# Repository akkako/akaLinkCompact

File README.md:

# akaLink Compact

* CMSIS-DAP v2.1 在线调试功能
  * SWD 接口
  * JTAG 接口
* VCOM 功能
  * 支持最高 1Mbps 收发
* 5V 输出功能
  * 支持外接隔离器

## TODO List

- [X] 移植 CMSIS-DAP
- [X] 优化 SWD 速度
- [ ] 优化 JTAG 性能
- [ ] 优化 VCOM 性能
- [ ] 更多速度选项
- [ ] Bootloader
- [X] HID 配置功能

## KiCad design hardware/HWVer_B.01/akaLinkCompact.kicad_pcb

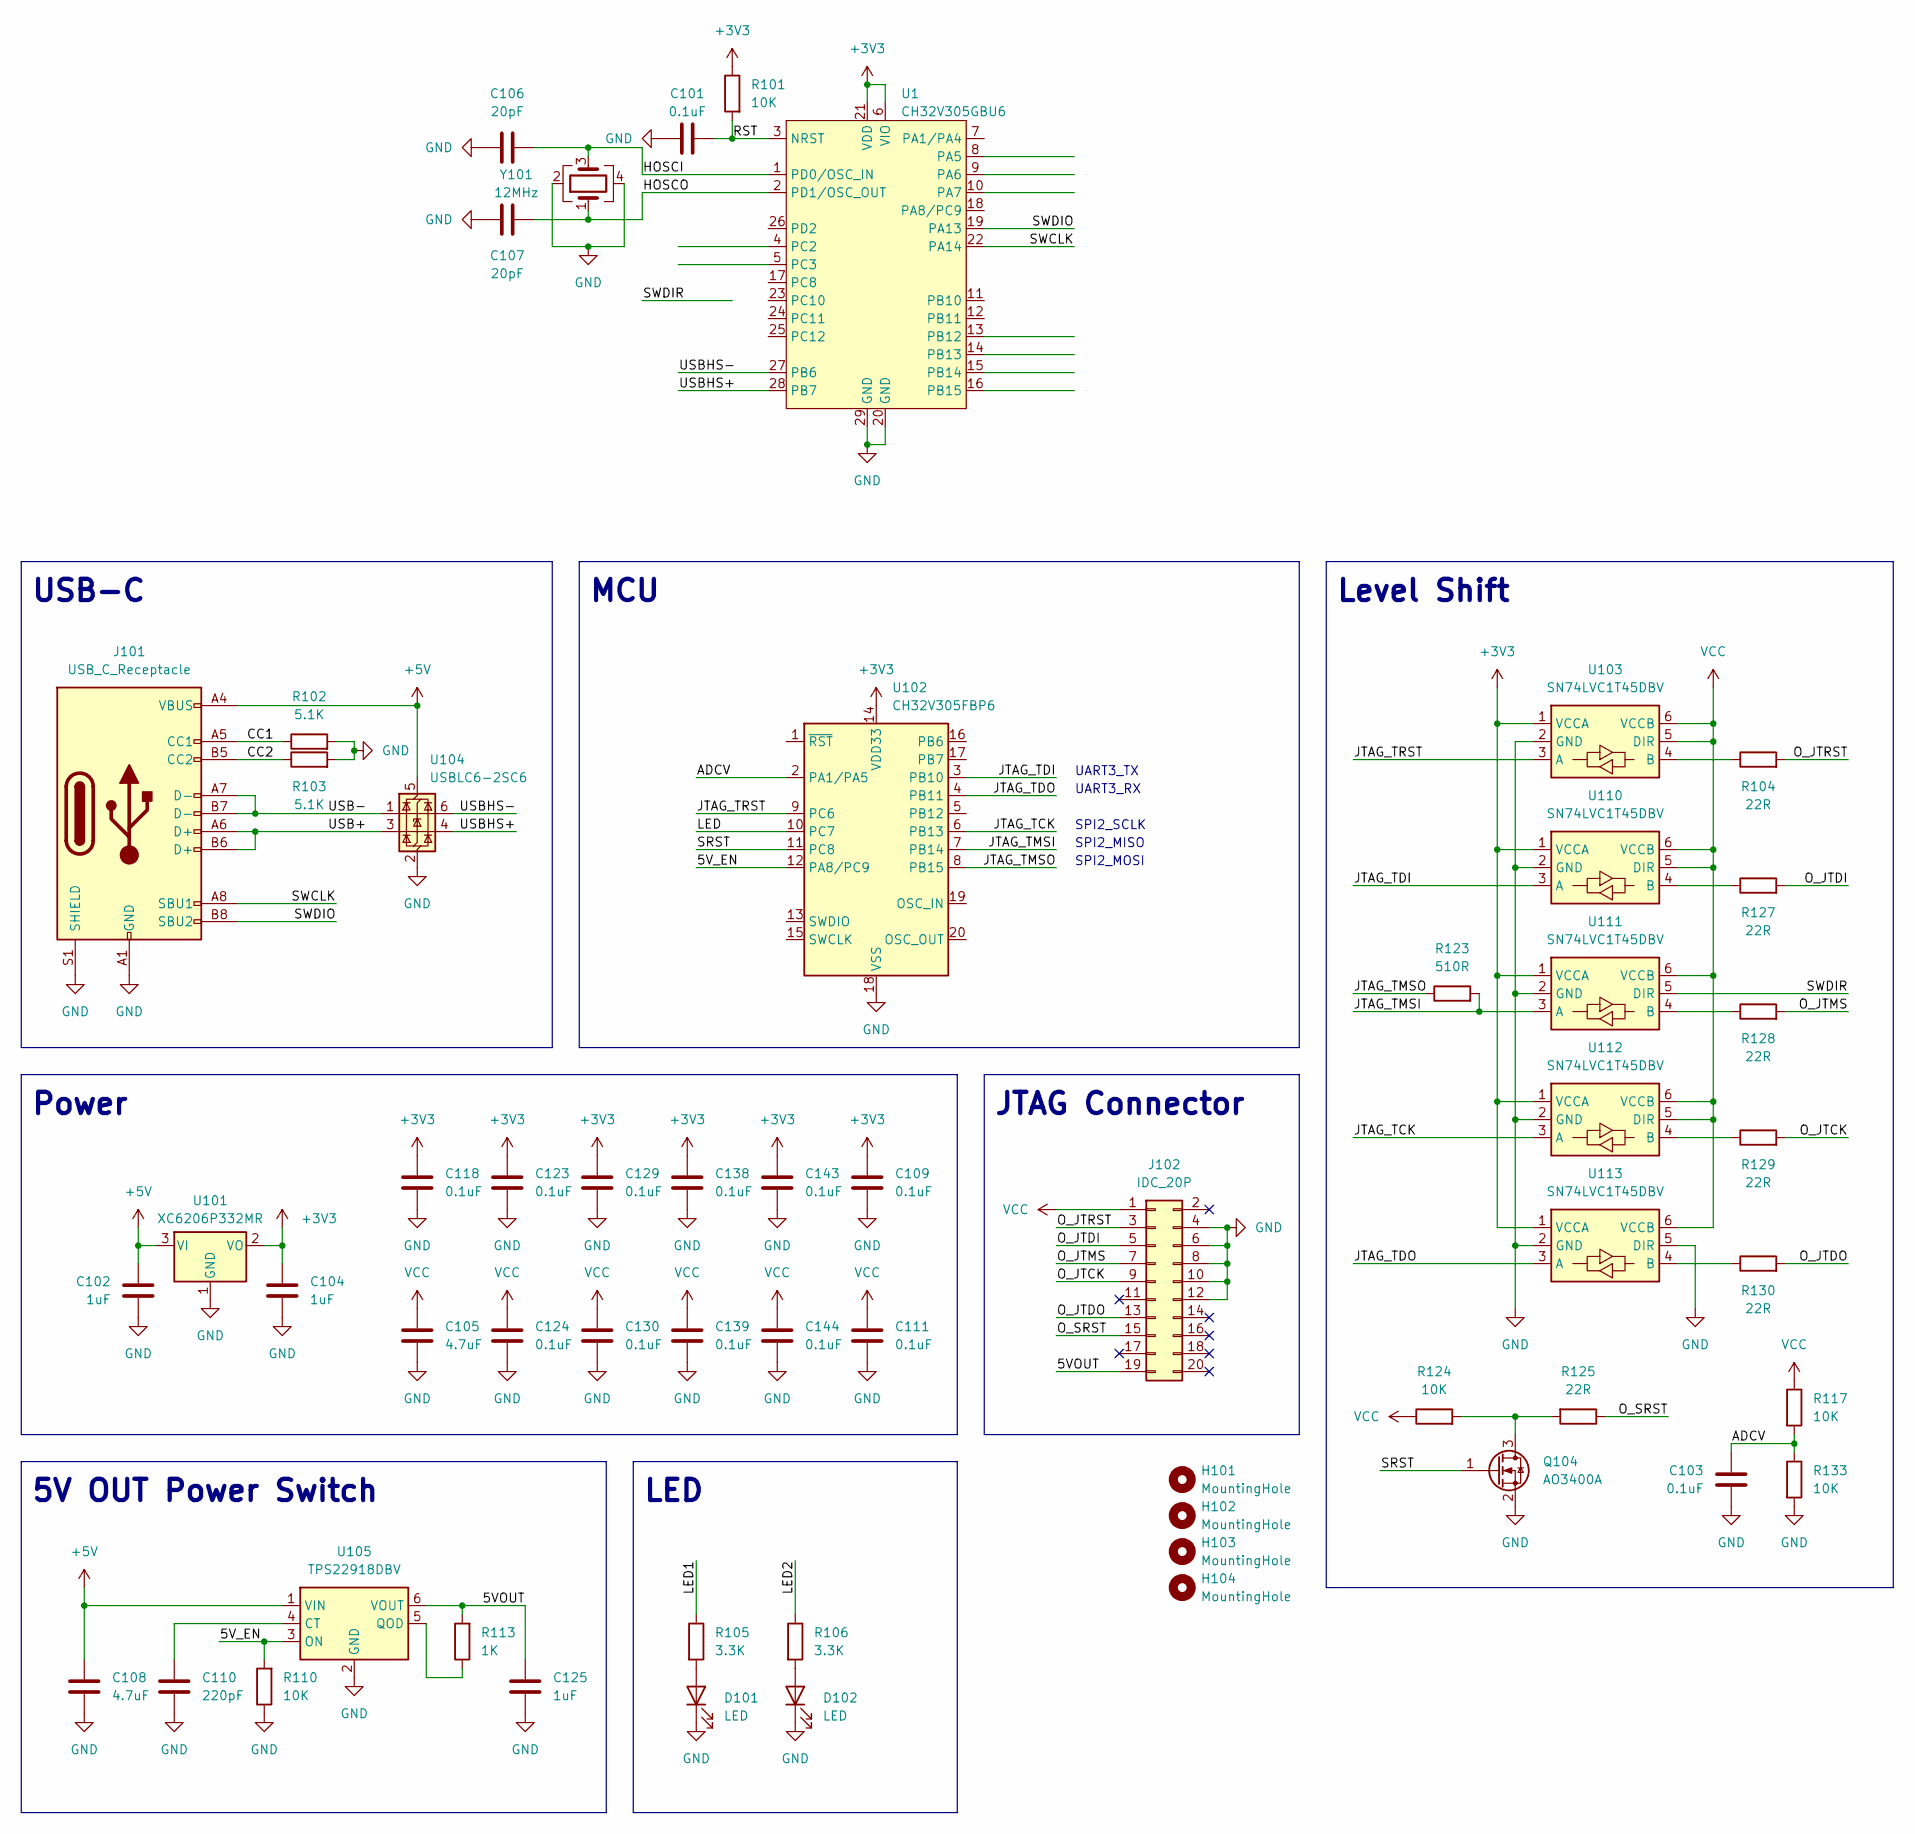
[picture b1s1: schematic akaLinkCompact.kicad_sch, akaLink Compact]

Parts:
C101, C103, C109, C111, C118, C123, C124, C129, C130, C138, C139, C143, C144: 0.1uF; C_0603_1608Metric
C102, C104, C125: 1uF; C_0603_1608Metric
C105, C108: 4.7uF; C_0603_1608Metric
C106, C107: 20pF; C_0603_1608Metric
C110: 220pF; C_0603_1608Metric
D101, D102: LED; LED_D3.0mm
H101, H102, H103, H104: MountingHole; MountingHole_2.5mm
J101: USB_C_Receptacle; USB_C_Receptacle_HRO_TYPE-C-31-M-12
J102: IDC_20P; IDC-Header_2x10_P2.54mm_Horizontal
Q104: AO3400A; SOT-23
R101, R110, R117, R124, R133: 10K; R_0603_1608Metric
R102, R103: 5.1K; R_0603_1608Metric
R104, R125, R127, R128, R129, R130: 22R; R_0603_1608Metric
R105, R106: 3.3K; R_0603_1608Metric
R113: 1K; R_0603_1608Metric
R123: 510R; R_0603_1608Metric
U1: CH32V305GBU6; WQFN-28-1EP_4x4mm_P0.4mm_EP2.7x2.7mm
U101: XC6206P332MR; SOT-23-3
U102: CH32V305FBP6; TSSOP-20_4.4x6.5mm_P0.65mm
U103, U110, U111, U112, U113: SN74LVC1T45DBV; SOT-23-6
U104: USBLC6-2SC6; SOT-23-6
U105: TPS22918DBV; SOT-23-6
Y101: 12MHz; Crystal_SMD_3225-4Pin_3.2x2.5mm

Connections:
+5V: C102.1, C108.1, J101.A4 (VBUS), J101.A9 (VBUS), J101.B4 (VBUS), J101.B9 (VBUS), U101.3 (VI), U104.5 (VBUS), U105.1 (VIN)
/5VOUT: C125.1, J102.19, R113.2, U105.6 (VOUT)
/5V_EN: R110.2, U102.12 (PA8/PC9), U105.3 (ON)
/ADCV: C103.1, R117.2, R133.1, U102.2 (PA1/PA5)
/CC1: J101.A5 (CC1), R102.1
/CC2: J101.B5 (CC2), R103.1
/HOSCI: C106.2, U1.1 (PD0/OSC_IN), U102.19 (OSC_IN), Y101.3
/HOSCO: C107.2, U1.2 (PD1/OSC_OUT), U102.20 (OSC_OUT), Y101.1
/JTAG_TCK: U102.6 (PB13), U112.3 (A)
/JTAG_TDI: U102.3 (PB10), U110.3 (A)
/JTAG_TDO: U102.4 (PB11), U113.3 (A)
/JTAG_TMSI: R123.2, U102.7 (PB14), U111.3 (A)
/JTAG_TMSO: R123.1, U102.8 (PB15)
/JTAG_TRST: U102.9 (PC6), U103.3 (A)
/O_JTCK: J102.9, R129.2
/O_JTDI: J102.5, R127.2
/O_JTDO: J102.13, R130.2
/O_JTMS: J102.7, R128.2
/O_JTRST: J102.3, R104.2
/O_SRST: J102.15, R125.1
/RST: C101.1, R101.2, U1.3 (NRST), U102.1 (~RST)
/SRST: Q104.1 (G), U102.11 (PC8)
/SWCLK: J101.A8 (SBU1), U1.22 (PA14), U102.15 (SWCLK)
/SWDIO: J101.B8 (SBU2), U1.19 (PA13), U102.13 (SWDIO)
/SWDIR: U102.5 (PB12), U111.5 (DIR)
/USB+: J101.A6 (D+), J101.B6 (D+), U104.3 (I/O2)
/USB-: J101.A7 (D-), J101.B7 (D-), U104.1 (I/O1)
/USBHS+: U1.28 (PB7), U102.17 (PB7), U104.4 (I/O2)
/USBHS-: U1.27 (PB6), U102.16 (PB6), U104.6 (I/O1)
GND: C101.2, C102.2, C103.2, C104.2, C105.2, C106.1, C107.1, C108.2, C109.2, C110.2, C111.2, C118.2, C123.2, C124.2, C125.2, C129.2, C130.2, C138.2, C139.2, C143.2, C144.2, D101.1 (K), D102.1 (K), J101.A1 (GND), J101.A12 (GND), J101.B1 (GND), J101.B12 (GND), J101.S1 (SHIELD), J102.4, J102.6, J102.8, J102.10, J102.12, Q104.2 (S), R102.2, R103.2, R110.1, R133.2, U1.20 (GND), U1.29 (GND), U101.1 (GND), U102.18 (VSS), U103.2 (GND), U104.2 (GND), U105.2 (GND), U110.2 (GND), U111.2 (GND), U112.2 (GND), U113.2 (GND), U113.5 (DIR), Y101.2, Y101.4
unnamed: D101.2 (A), R105.2
unnamed: D102.2 (A), R106.2
unnamed: Q104.3 (D), R124.2, R125.2
unnamed: R104.1, U103.4 (B)
unnamed: C110.1, U105.4 (CT)
unnamed: R113.1, U105.5 (QOD)
unnamed: R127.1, U110.4 (B)
unnamed: R128.1, U111.4 (B)
unnamed: R129.1, U112.4 (B)
unnamed: R130.1, U113.4 (B)
VCC: C105.1, C111.1, C124.1, C130.1, C139.1, C144.1, J102.1, R117.1, R124.1, U103.5 (DIR), U103.6 (VCCB), U110.5 (DIR), U110.6 (VCCB), U111.6 (VCCB), U112.5 (DIR), U112.6 (VCCB), U113.6 (VCCB)

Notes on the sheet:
SPI2_MOSI
Level Shift
5V OUT Power Switch
LED
USB-C
JTAG Connector
UART3_RX
SPI2_MISO
Power
SPI2_SCLK
UART3_TX
MCU

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
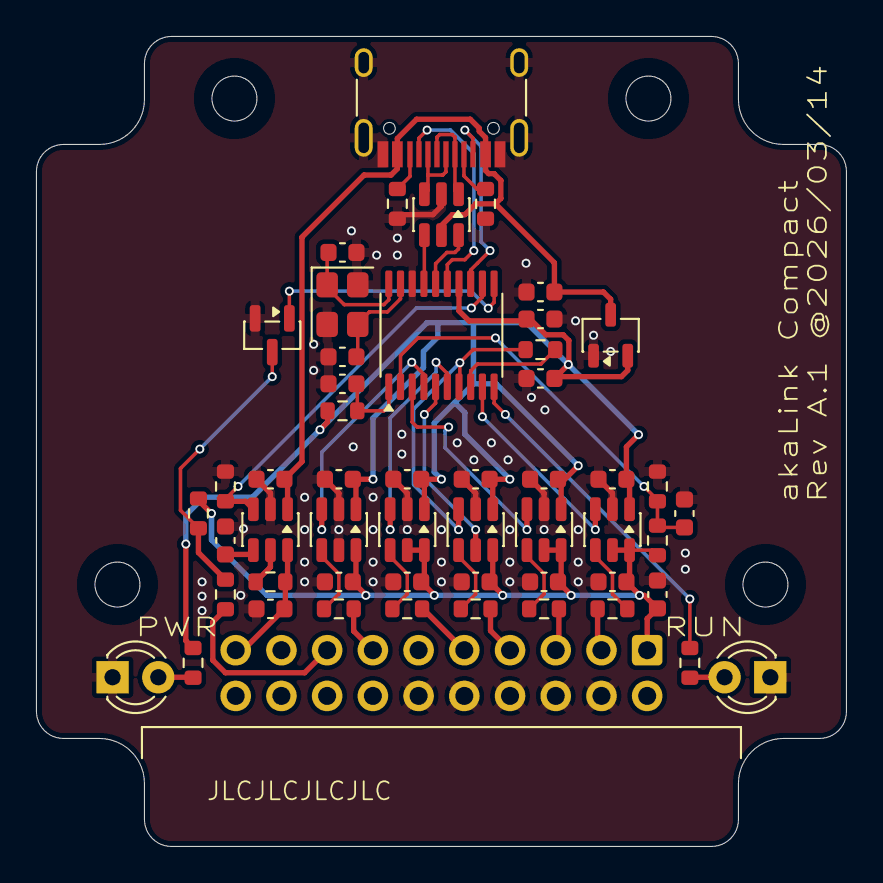
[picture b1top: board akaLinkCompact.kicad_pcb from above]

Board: 2 copper layers, 45.0 x 45.0 mm, 57 parts (0 on the bottom side), 43 nets.

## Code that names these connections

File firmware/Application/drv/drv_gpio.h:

#ifndef __DRV_GPIO_H__
#define __DRV_GPIO_H__

#include <stdint.h>
#include "ch32v30x_gpio.h"

// -------------------------------------------------------------
// | Pin name | Pin loc  | funtion1   | funtion2   | Pin alt   |
// | -------- | -------- | ---------- | ---------- | --------- |
// | ADCV     | PA1      |            |            | ADC_CH1   |
// | TRST     | PC6      | JTAG_TRST  | N/A(INPUT) | GPIO      |
// | LED      | PC7      |            |            | GPIO      |
// | SRST     | PC8      |            |            | GPIO      |
// | 5VEN     | PC9      |            |            | GPIO      |
// | TDI      | PB10     | JTAG_TDI   | UART_TXD   | UART3_TXD |
// | TDO      | PB11     | JTAG_TDO   | UART_RXD   | UART3_RXD |
// | SWDIR    | PB12     | N/A(HIGH)  | SWDIR      | GPIO      |
// | TCK      | PB13     | JTAG_TCK   | SWCLK      | SPI2_SCLK |
// | TMSI     | PB14     | N/A(INPUT) | SWDI       | SPI2_MISO |
// | TMSO     | PB15     | JTAG_TMS   | SWDO       | SPI2_MOSI |
// |          |          |            |            |           |
// -------------------------------------------------------------

#ifdef __cplusplus
extern "C"
{
#endif

    /**
     * @brief 设置 TRST 引脚为高电平
     *
     */
    static inline void drv_gpio_set_trst(void)
    {
        GPIO_SetBits(GPIOC, GPIO_Pin_6);
    }

    /**
     * @brief 设置 TRST 引脚为低电平
     *
     */
    static inline void drv_gpio_reset_trst(void)
    {
        GPIO_ResetBits(GPIOC, GPIO_Pin_6);
    }

    /**
     * @brief 设置 SRST 引脚为高电平（驱动 MOS 反相）
     *
     */
    static inline void drv_gpio_set_srst(void)
    {
        GPIO_ResetBits(GPIOC, GPIO_Pin_8);
    }

    /**
     * @brief 设置 SRST 引脚为低电平（驱动 MOS 反相）
     *
     */
    static inline void drv_gpio_reset_srst(void)
    {
        GPIO_SetBits(GPIOC, GPIO_Pin_8);
    }

    /**
     * @brief 设置 5VEN 引脚为高电平
     *
     */
    static inline void drv_gpio_set_5ven(void)
    {
        GPIO_SetBits(GPIOC, GPIO_Pin_9);
    }

    /**
     * @brief 设置 5VEN 引脚为低电平
     *
     */
    static inline void drv_gpio_reset_5ven(void)
    {
        GPIO_ResetBits(GPIOC, GPIO_Pin_9);
    }

    /**
     * @brief 设置 LED 引脚为高电平
     *
     */
    static inline void drv_gpio_set_led(void)
    {
        GPIO_SetBits(GPIOC, GPIO_Pin_7);
    }

    /**
     * @brief 设置 LED 引脚为低电平
     *
     */
    static inline void drv_gpio_reset_led(void)
    {
        GPIO_ResetBits(GPIOC, GPIO_Pin_7);
    }

    /**
     * @brief 设置 SWDIR 引脚为高电平
     *
     */
    static inline void drv_gpio_set_swdir(void)
    {
        GPIO_SetBits(GPIOB, GPIO_Pin_12);
    }

    /**
     * @brief 设置 SWDIR 引脚为低电平
     *
     */
    static inline void drv_gpio_reset_swdir(void)
    {
        GPIO_ResetBits(GPIOB, GPIO_Pin_12);
    }

    /**
     * @brief 设置 TDI 引脚为高电平
     *
     */
    static inline void drv_gpio_set_tdi(void)
    {
        GPIO_SetBits(GPIOB, GPIO_Pin_10);
    }

    /**
     * @brief 设置 TDI 引脚为低电平
     *
     */
    static inline void drv_gpio_reset_tdi(void)
    {
        GPIO_ResetBits(GPIOB, GPIO_Pin_10);
    }

    /**
     * @brief 设置 TCK 引脚为高电平
     *
     */
    static inline void drv_gpio_set_tck(void)
    {
        GPIO_SetBits(GPIOB, GPIO_Pin_13);
    }

    /**
     * @brief 设置 TCK 引脚为低电平
     *
     */
    static inline void drv_gpio_reset_tck(void)
    {
        GPIO_ResetBits(GPIOB, GPIO_Pin_13);
    }

    /**
     * @brief 设置 TMSO 引脚为高电平
     *
     */
    static inline void drv_gpio_set_tmso(void)
    {
        GPIO_SetBits(GPIOB, GPIO_Pin_15);
    }

    /**
     * @brief 设置 TMSO 引脚为低电平
     *
     */
    static inline void drv_gpio_reset_tmso(void)
    {
        GPIO_ResetBits(GPIOB, GPIO_Pin_15);
    }

    void drv_gpio_init_as_hiz(void);
    void drv_gpio_init_as_jtag(void);
    void drv_gpio_init_as_swd_uart(void);

#ifdef __cplusplus
}
#endif

#endif

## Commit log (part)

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2026-02-12 add project
2026-03-18 add hardware
2026-03-18 modify firmware
2026-03-18 refactor(usb): 简化USB配置并移除未使用的功能
    移除MSC和WebUSB相关代码，优化USB端点配置
    更新链接脚本和调试输出级别，调整序列号长度
2026-03-18 feat: 添加RTT调试接口并优化SWD传输逻辑
    重构GPIO驱动，移除SPI相关代码
    添加RTT调试端点配置
    优化SWD传输性能，移除冗余代码
    更新项目配置和工具链版本
2026-03-19 refactor(gpio): 优化GPIO配置实现方式 fix(usb): 调整HID数据包大小并添加自定义HID支持
2026-03-19 add develop firmware project
2026-03-19 add usb hid tool
2026-03-19 update dev project
2026-05-11 remove unused project
2026-05-20 add spi swd port
2026-05-20 opt spi swd
2026-05-20 optimize code
2026-05-20 remove old code
2026-05-20 port jtag pin driver
2026-05-21 optimize timming
2026-05-21 optimize swd timming
2026-05-22 optimize swd timming add uart comment
2026-05-24 refactor uart function
2026-05-24 port uart
2026-05-28 fix uart usbtx bug
2026-05-29 build: add sys config and adjust build includes
    1. 新增系统配置头文件sys_config.h并添加相关编译宏
    2. 向应用层Makefile和工程配置中添加sys目录头文件引用
    3. 重构usb转uart驱动，新增空闲中断配置宏与处理函数
    4. 优化usb主循环中uart数据处理流程
2026-06-01 add hid port
2026-06-01 fix hid enum, add webhid debug
2026-06-01 add hid protocol
2026-06-01 modify hid protocol
2026-06-02 add hid implimentation
2026-06-02 change docs name
2026-06-03 update protocol
2026-06-03 add webui
2026-06-03 fix webui hid protocol
2026-06-03 fix webui theme sync
2026-06-03 add more inromation display
2026-06-03 fix webui reconnect fail
2026-06-03 update bootloader
2026-06-06 update pack script and workflow
2026-06-06 update workflow
2026-06-06 update makefile
2026-06-06 update makefile OS detect
2026-06-06 update action
2026-06-06 test workflow
2026-06-06 refactor(dap): 清理冗余代码并调整DAP初始化参数
    1. 移除JTAG_DP.c中多余空行和SWD宏定义
    2. 移除main.c中冗余printf和空行
    3. 调整DAP_Setup参数传入输出模式
    4. 增大DAP包缓冲数量到8
    5. 重构SW_DP.c中条件编译代码
    6. 更新DAP结构体和函数声明
2026-06-07 update webui and hid protocol
2026-06-08 update webui
2026-06-09 add new hardware
2026-06-09 add webusb and msc
2026-06-09 update adress plan
2026-06-11 optimize dap impl
2026-06-11 add test asm
2026-06-11 add some regster level operation
2026-06-14 add gpio sim swd
2026-06-15 add gpio opt asm
2026-06-15 update gpio asm
2026-06-16 optimize asm
